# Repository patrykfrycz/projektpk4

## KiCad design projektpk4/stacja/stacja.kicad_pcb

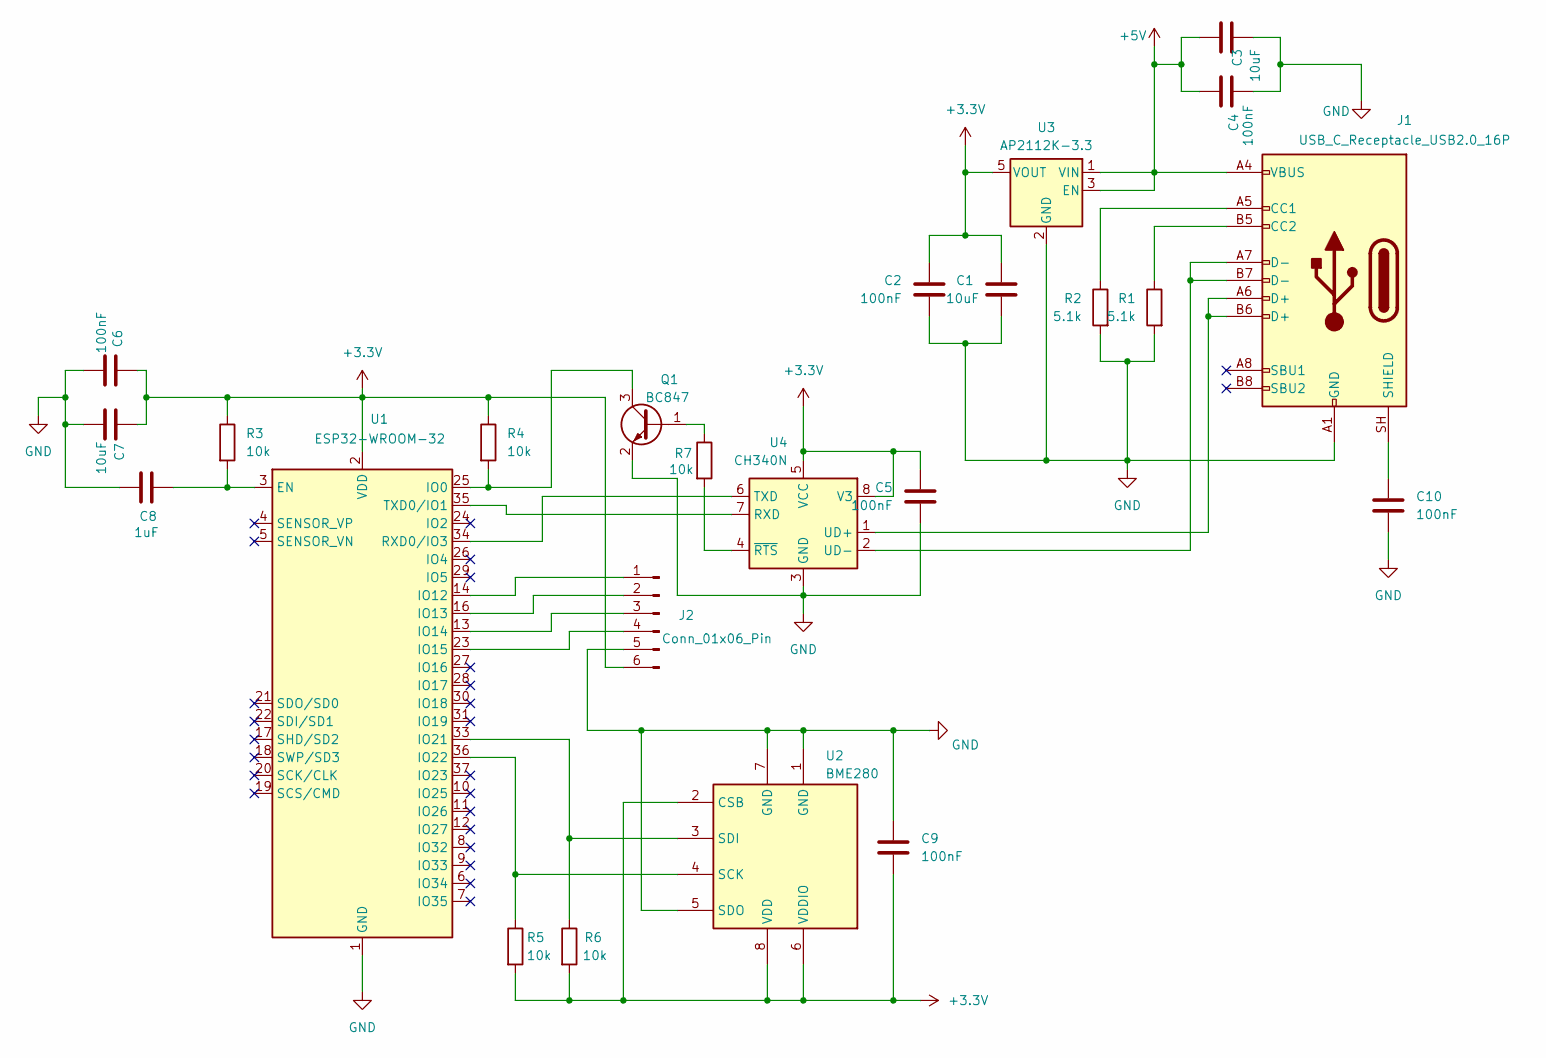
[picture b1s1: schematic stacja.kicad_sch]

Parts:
C1, C3, C7: 10uF; C_0805_2012Metric
C2, C4, C5, C6, C9, C10: 100nF; C_0805_2012Metric
C8: 1uF; C_0805_2012Metric
J1: USB_C_Receptacle_USB2.0_16P; USB_C_Receptacle_GCT_USB4110
J2: Conn_01x06_Pin; PinHeader_1x06_P2.54mm_Vertical
Q1: BC847; SOT-23
R1, R2: 5.1k; R_0805_2012Metric
R3, R4, R5, R6, R7: 10k; R_0805_2012Metric
U1: ESP32-WROOM-32
U2: BME280; Bosch_LGA-8_2.5x2.5mm_P0.65mm_ClockwisePinNumbering
U3: AP2112K-3.3; SOT-23-5
U4: CH340N; JEITA_SOIC-8_3.9x4.9mm_P1.27mm

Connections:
+3.3V: C1.1, C2.1, C5.1, C6.1, C7.1, C9.2, J2.6, R3.1, R4.1, R5.2, R6.2, U1.2 (VDD), U2.2 (CSB), U2.6 (VDDIO), U2.8 (VDD), U3.5 (VOUT), U4.5 (VCC), U4.8 (V3)
+5V: C3.1, C4.1, J1.A4 (VBUS), J1.A9 (VBUS), J1.B4 (VBUS), J1.B9 (VBUS), U3.1 (VIN), U3.3 (EN)
GND: C1.2, C2.2, C3.2, C4.2, C5.2, C6.2, C7.2, C8.2, C9.1, C10.2, J1.A1 (GND), J1.A12 (GND), J1.B1 (GND), J1.B12 (GND), J2.5, Q1.2 (E), R1.2, R2.2, U1.1 (GND), U1.15 (GND), U1.38 (GND), U1.39 (GND), U2.1 (GND), U2.5 (SDO), U2.7 (GND), U3.2 (GND), U4.3 (GND)
unnamed: J1.A5 (CC1), R2.1
unnamed: J1.B5 (CC2), R1.1
unnamed: C10.1, J1.SH (SHIELD)
unnamed: J2.1, U1.14 (IO12)
unnamed: J2.2, U1.16 (IO13)
unnamed: J2.3, U1.13 (IO14)
unnamed: J2.4, U1.23 (IO15)
unnamed: Q1.1 (B), R7.1
unnamed: Q1.3 (C), R4.2, U1.25 (IO0)
unnamed: C8.1, R3.2, U1.3 (EN)
unnamed: R6.1, U1.33 (IO21), U2.3 (SDI)
unnamed: R5.1, U1.36 (IO22), U2.4 (SCK)
unnamed: U1.34 (RXD0/IO3), U4.6 (TXD)
unnamed: U1.35 (TXD0/IO1), U4.7 (RXD)
unnamed: J1.A6 (D+), J1.B6 (D+), U4.1 (UD+)
unnamed: J1.A7 (D-), J1.B7 (D-), U4.2 (UD-)
unnamed: R7.2, U4.4 (~RTS)

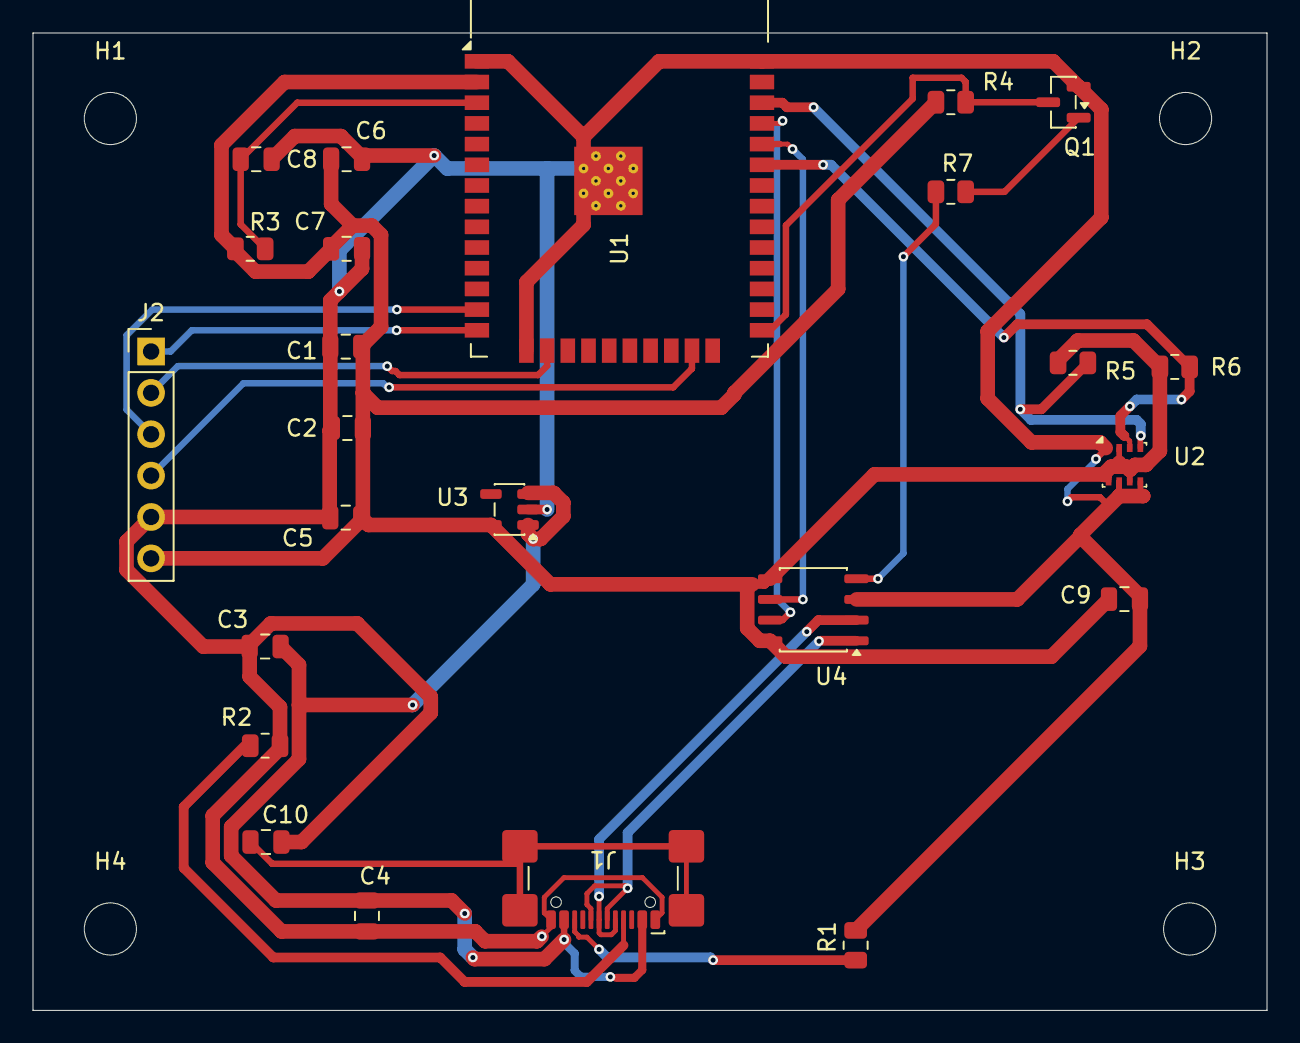
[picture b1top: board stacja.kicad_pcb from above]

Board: 2 copper layers, 75.7 x 60.0 mm, 28 parts (0 on the bottom side), 20 nets.

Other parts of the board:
H1, H2, H3, H4: 3.2mm_M3; MountingHole_3.2mm_M3

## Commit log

2026-03-17 Dodaj .gitattributes i .gitignore.
2026-03-17 Dodaj pliki projektów.
2026-03-19 przycisk play i ekrany
2026-03-24 menu glowne
2026-03-26 Menu i przyciski
2026-04-21 Changes - World, Platform ect.
2026-04-21 platforma
2026-04-23 skakanie i gameover
2026-04-27 Changes.
2026-05-06 enemy
2026-05-09 moby
2026-05-25 mario sprite
2026-06-01 troopa
2026-06-02 menu
2026-06-05 mysteryblocks
2026-06-12 ranges
2026-06-14 dziwiek
2026-06-14 tabela
2026-06-15 polimorfizm
